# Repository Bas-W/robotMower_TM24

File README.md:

# robotMower_TM24
Robot lawn mower project for school.

# Notes
Some notes including the lessons we learned and the mistakes we found in our work can be found under [<b>*/Notes*</b>](/Notes.md)\
This contains some important information for anyone who wants to expand this project, **Please read this document**.

# Features
A list of features can be found under [<b>*/Features*</b>](/Features.md)

# Schematics, PCB
Schematics, along with footprints, can be found under [<b>*/Schematics*</b>](/Schematics).
These are designed in Fusion 360/Eagle, original Fusion/eagle Schematic, board and library files can be found under [***/Schematics/RoborMower_TM24/***](/Schematics/RoborMower_TM24/)

# Code
Code can be found under [***/Code***](/Code).
The final code for the ESP32 can be found under [***/Code/Final_V1.0***](/Code/Final_V1.0.0/).
The final code for the Attiny that read the HC-SR04 sensor can be fount under [***/Code/Test Sketches/ATtiny84_I2C-Slave-Ultrasonic_Test/***](/Code/Test%20Sketches/ATtiny84_I2C-Slave-Ultrasonic_Test/).

# Harware
A list of used components and modules will be made when the design is finalized.

# I²C Adress List
|Part|Address|
|----|-------|
|Current Sensor, Motor L|01000000 = 0x40|
|Current Sensor, Motor R|01000001 = 0x41|
|Current Sensor, Bat in|01000010 = 0x42|
|Current Sensor, 5V|01000011 = 0x43|
|Current Sensor, 3V3|01000100 = 0x44|
|Attiny, Ultrasone Sensors|00001000 = 0x8|

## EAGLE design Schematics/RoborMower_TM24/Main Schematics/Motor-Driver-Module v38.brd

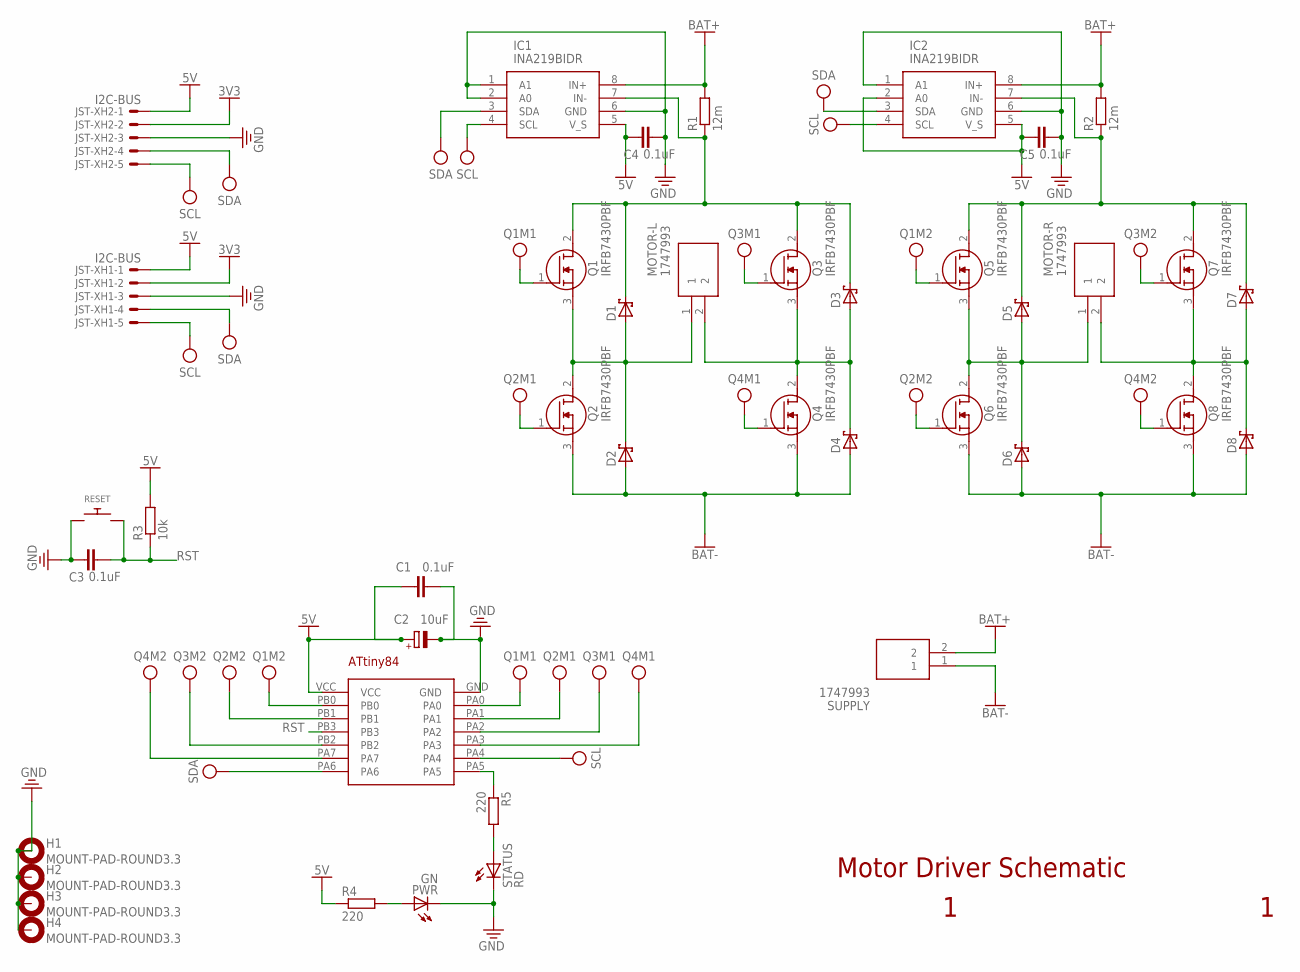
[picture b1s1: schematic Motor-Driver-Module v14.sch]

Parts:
C1: 0.1uF; C025-025X050
C2: 10uF; E5-10,5
C3, C4, C5: 0.1uF; C025-030X050
D1, D2, D3, D4, D5, D6, D7, D8: SCHOTTKY-DIODEDO41; DO41-10
H1, H2, H3, H4: MOUNT-PAD-ROUND3.3; 3,3-PAD
IC1, IC2: INA219BIDR; SOIC127P600X175-8N
JST-XH1, JST-XH2: I2C-BUS; JST-XH-05-PACKAGE-LONG-PAD
MOTOR-L: 1747993
MOTOR-R: 1747993
PWR: GN; LED5MM
Q1, Q2, Q3, Q4, Q5, Q6, Q7, Q8: IRFB7430PBF; TO254P483X1016X1994-3P
R1, R2: 12m; 0204/7
R3: 10k; 0204/7
R4, R5: 220; 0204/7
RESET: SWITCH_PUSHBUTTONEVQ-PE; TACT_PANA-EVQ
STATUS: RD; LED5MM
SUPPLY: 1747993
U$1: ATTINY84DIP; ATTINY84(DIP)

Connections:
3V3: JST-XH1.2, JST-XH2.2
5V: C1.1, C2.+, C4.1, C5.1, IC1.5 (V_S), IC2.2 (A0), IC2.5 (V_S), JST-XH1.1, JST-XH2.1, R3.2, R4.1, U$1.VCC
BAT+: IC1.8 (IN+), IC2.8 (IN+), R1.2, R2.2, SUPPLY.2
BAT-: D2.A, D4.A, D6.A, D8.A, Q2.3 (S), Q4.3 (S), Q6.3 (S), Q8.3 (S), SUPPLY.1
GND: C1.2, C2.-, C3.1, C4.2, C5.2, H1.B3,3, H2.B3,3, H3.B3,3, H4.B3,3, IC1.1 (A1), IC1.2 (A0), IC1.6 (GND), IC2.1 (A1), IC2.6 (GND), JST-XH1.3, JST-XH2.3, PWR.K (C), RESET.P$1, STATUS.K (C), U$1.GND
unnamed: D3.A, D4.C, MOTOR-L.2, Q3.3 (S), Q4.2 (D)
unnamed: D1.A, D2.C, MOTOR-L.1, Q1.3 (S), Q2.2 (D)
unnamed: D7.A, D8.C, MOTOR-R.2, Q7.3 (S), Q8.2 (D)
unnamed: D5.A, D6.C, MOTOR-R.1, Q5.3 (S), Q6.2 (D)
unnamed: D1.C, D3.C, IC1.7 (IN-), Q1.2 (D), Q3.2 (D), R1.1
unnamed: D5.C, D7.C, IC2.7 (IN-), Q5.2 (D), Q7.2 (D), R2.1
unnamed: R5.1, U$1.PA5
unnamed: R5.2, STATUS.A
unnamed: PWR.A, R4.2
Q1M1: Q1.1 (G), U$1.PA0
Q1M2: Q5.1 (G), U$1.PB0
Q2M1: Q2.1 (G), U$1.PA1
Q2M2: Q6.1 (G), U$1.PB1
Q3M1: Q3.1 (G), U$1.PA2
Q3M2: Q7.1 (G), U$1.PB2
Q4M1: Q4.1 (G), U$1.PA3
Q4M2: Q8.1 (G), U$1.PA7
RST: C3.2, R3.1, RESET.P$2, U$1.PB3
SCL: IC1.4 (SCL), IC2.4 (SCL), JST-XH1.5, JST-XH2.5, U$1.PA4
SDA: IC1.3 (SDA), IC2.3 (SDA), JST-XH1.4, JST-XH2.4, U$1.PA6

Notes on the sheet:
Motor Driver Schematic

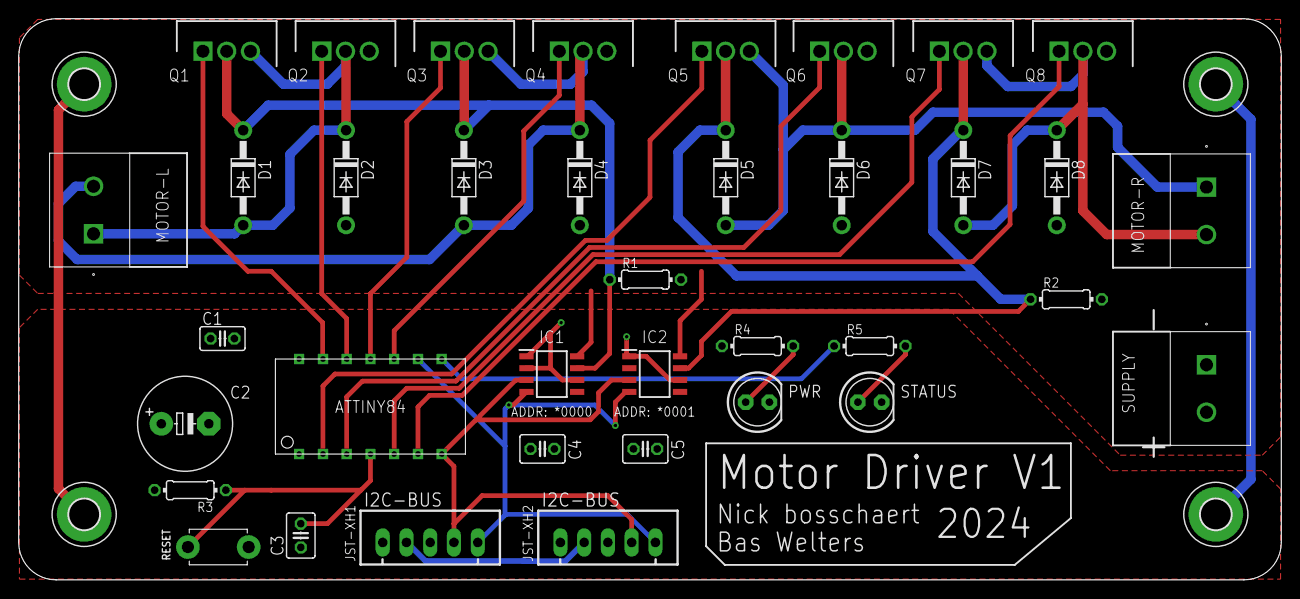
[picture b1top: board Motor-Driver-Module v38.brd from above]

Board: 2 copper layers, 135.0 x 60.0 mm, 41 parts (0 on the bottom side), 25 nets.

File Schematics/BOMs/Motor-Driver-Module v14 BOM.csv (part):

Part;Value;Device;Package;Description;ARROW_PART_NUMBER;ARROW_PRICE-STOCK;DESCRIPTION;HEIGHT;MANUFACTURER_NAME;MANUFACTURER_PART_NUMBER;MOUSER_PART_NUMBER;MOUSER_PRICE-STOCK;POPULARITY;SPICEPREFIX
C1;0.1uF;C-EU025-025X050;C025-025X050;CAPACITOR, European symbol;;;;;;;;;65;C
C2;10uF;CPOL-EUE5-10.5;E5-10,5;POLARIZED CAPACITOR, European symbol;;;;;;;;;23;C
C3;0.1uF;C-EU025-030X050;C025-030X050;CAPACITOR, European symbol;;;;;;;;;14;C
C4;0.1uF;C-EU025-030X050;C025-030X050;CAPACITOR, European symbol;;;;;;;;;14;C
C5;0.1uF;C-EU025-030X050;C025-030X050;CAPACITOR, European symbol;;;;;;;;;14;C
D1;;SCHOTTKY-DIODEDO41;DO41-10;Schottky Diode;;;;;;;;;;
D2;;SCHOTTKY-DIODEDO41;DO41-10;Schottky Diode;;;;;;;;;;
D3;;SCHOTTKY-DIODEDO41;DO41-10;Schottky Diode;;;;;;;;;;
D4;;SCHOTTKY-DIODEDO41;DO41-10;Schottky Diode;;;;;;;;;;
D5;;SCHOTTKY-DIODEDO41;DO41-10;Schottky Diode;;;;;;;;;;
D6;;SCHOTTKY-DIODEDO41;DO41-10;Schottky Diode;;;;;;;;;;
D7;;SCHOTTKY-DIODEDO41;DO41-10;Schottky Diode;;;;;;;;;;
D8;;SCHOTTKY-DIODEDO41;DO41-10;Schottky Diode;;;;;;;;;;
H1;MOUNT-PAD-ROUND3.3;MOUNT-PAD-ROUND3.3;3,3-PAD;MOUNTING PAD, round;;;;;;;;;1;
H2;MOUNT-PAD-ROUND3.3;MOUNT-PAD-ROUND3.3;3,3-PAD;MOUNTING PAD, round;;;;;;;;;1;
H3;MOUNT-PAD-ROUND3.3;MOUNT-PAD-ROUND3.3;3,3-PAD;MOUNTING PAD, round;;;;;;;;;1;
H4;MOUNT-PAD-ROUND3.3;MOUNT-PAD-ROUND3.3;3,3-PAD;MOUNTING PAD, round;;;;;;;;;1;
IC1;INA219BIDR;INA219BIDR;SOIC127P600X175-8N;26-V, Bidirectional, Zero-Drift, High-Side, I2C Out Current/Power Monitor;;;26-V, Bidirectional, Zero-Drift, High-Side, I2C Out Current/Power Monitor;1.75mm;Texas Instruments;INA219BIDR;595-INA219BIDR;https://www.mouser.co.uk/ProductDetail/Texas-Instruments/INA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;;
IC2;INA219BIDR;INA219BIDR;SOIC127P600X175-8N;26-V, Bidirectional, Zero-Drift, High-Side, I2C Out Current/Power Monitor;;;26-V, Bidirectional, Zero-Drift, High-Side, I2C Out Current/Power Monitor;1.75mm;Texas Instruments;INA219BIDR;595-INA219BIDR;https://www.mouser.co.uk/ProductDetail/Texas-Instruments/INA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;;
JST-XH1;I2C-BUS;JST-XH-05-PIN-LONG-PAD;JST-XH-05-PACKAGE-LONG-PAD;JST XH Connector 2 Pin;;;;;;;;;;
JST-XH2;I2C-BUS;JST-XH-05-PIN-LONG-PAD;JST-XH-05-PACKAGE-LONG-PAD;JST XH Connector 2 Pin;;;;;;;;;;
MOTOR-L;1747993;1747993;1747993;PCB header, nominal cross section: 2.5 mm?, color: green, nominal current: 12 A, rated voltage (III/2): 320 V, contact surface: Gold, type of contact: Male connector, Number of potentials: 2, Number of rows: 1, Number of positions per row: 2, number of connections: 2, product range: MSTBVA 2,5/..-G, pitch: 5.08 mm, mounting: Wave soldering, pin layout: Linear pinning, solder pin [P]: 3.9 mm, Stecksystem: CLASSIC COMBICON, Locking: without, type of packaging: packed in cardboard;;;PCB header, nominal cross section: 2.5 mm?, color: green, nominal current: 12 A, rated voltage (III/2): 320 V, contact surface: Gold, type of contact: Male connector, Number of potentials: 2, Number of rows: 1, Number of positions per row: 2, number of connections: 2, product range: MSTBVA 2,5/..-G, pitch: 5.08 mm, mounting: Wave soldering, pin layout: Linear pinning, solder pin [P]: 3.9 mm, Stecksystem: CLASSIC COMBICON, Locking: without, type of packaging: packed in cardboard;12.15mm;Phoenix Contact;1747993;651-1747993;https://www.mouser.co.uk/ProductDetail/Phoenix-Contact/17479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;;
MOTOR-R;1747993;1747993;1747993;PCB header, nominal cross section: 2.5 mm?, color: green, nominal current: 12 A, rated voltage (III/2): 320 V, contact surface: Gold, type of contact: Male connector, Number of potentials: 2, Number of rows: 1, Number of positions per row: 2, number of connections: 2, product range: MSTBVA 2,5/..-G, pitch: 5.08 mm, mounting: Wave soldering, pin layout: Linear pinning, solder pin [P]: 3.9 mm, Stecksystem: CLASSIC COMBICON, Locking: without, type of packaging: packed in cardboard;;;PCB header, nominal cross section: 2.5 mm?, color: green, nominal current: 12 A, rated voltage (III/2): 320 V, contact surface: Gold, type of contact: Male connector, Number of potentials: 2, Number of rows: 1, Number of positions per row: 2, number of connections: 2, product range: MSTBVA 2,5/..-G, pitch: 5.08 mm, mounting: Wave soldering, pin layout: Linear pinning, solder pin [P]: 3.9 mm, Stecksystem: CLASSIC COMBICON, Locking: without, type of packaging: packed in cardboard;12.15mm;Phoenix Contact;1747993;651-1747993;https://www.mouser.co.uk/ProductDetail/Phoenix-Contact/17479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;;
PWR;GN;LED5MM;LED5MM;LED;;;;;;;;;;
Q1;IRFB7430PBF;IRFB7430PBF;TO254P483X1016X1994-3P;Infineon IRFB7430PBF N-channel MOSFET, 195 A, 40 V StrongIRFET, 3-Pin TO-220AB;;;Infineon IRFB7430PBF N-channel MOSFET, 195 A, 40 V StrongIRFET, 3-Pin TO-220AB;4.83mm;Infineon;IRFB7430PBF;942-IRFB7430PBF;https://www.mouser.co.uk/ProductDetail/Infineon-Technologies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;;
Q2;IRFB7430PBF;IRFB7430PBF;TO254P483X1016X1994-3P;Infineon IRFB7430PBF N-channel MOSFET, 195 A, 40 V StrongIRFET, 3-Pin TO-220AB;;;Infineon IRFB7430PBF N-channel MOSFET, 195 A, 40 V StrongIRFET, 3-Pin TO-220AB;4.83mm;Infineon;IRFB7430PBF;942-IRFB7430PBF;https://www.mouser.co.uk/ProductDetail/Infineon-Technologies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;;
Q3;IRFB7430PBF;IRFB7430PBF;TO254P483X1016X1994-3P;Infineon IRFB7430PBF N-channel MOSFET, 195 A, 40 V StrongIRFET, 3-Pin TO-220AB;;;Infineon IRFB7430PBF N-channel MOSFET, 195 A, 40 V StrongIRFET, 3-Pin TO-220AB;4.83mm;Infineon;IRFB7430PBF;942-IRFB7430PBF;https://www.mouser.co.uk/ProductDetail/Infineon-Technologies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;;
Q4;IRFB7430PBF;IRFB7430PBF;TO254P483X1016X1994-3P;Infineon IRFB7430PBF N-channel MOSFET, 195 A, 40 V StrongIRFET, 3-Pin TO-220AB;;;Infineon IRFB7430PBF N-channel MOSFET, 195 A, 40 V StrongIRFET, 3-Pin TO-220AB;4.83mm;Infineon;IRFB7430PBF;942-IRFB7430PBF;https://www.mouser.co.uk/ProductDetail/Infineon-Technologies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;;
Q5;IRFB7430PBF;IRFB7430PBF;TO254P483X1016X1994-3P;Infineon IRFB7430PBF N-channel MOSFET, 195 A, 40 V StrongIRFET, 3-Pin TO-220AB;;;Infineon IRFB7430PBF N-channel MOSFET, 195 A, 40 V StrongIRFET, 3-Pin TO-220AB;4.83mm;Infineon;IRFB7430PBF;942-IRFB7430PBF;https://www.mouser.co.uk/ProductDetail/Infineon-Technologies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;;
Q6;IRFB7430PBF;IRFB7430PBF;TO254P483X1016X1994-3P;Infineon IRFB7430PBF N-channel MOSFET, 195 A, 40 V StrongIRFET, 3-Pin TO-220AB;;;Infineon IRFB7430PBF N-channel MOSFET, 195 A, 40 V StrongIRFET, 3-Pin TO-220AB;4.83mm;Infineon;IRFB7430PBF;942-IRFB7430PBF;https://www.mouser.co.uk/ProductDetail/Infineon-Technologies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;;
Q7;IRFB7430PBF;IRFB7430PBF;TO254P483X1016X1994-3P;Infineon IRFB7430PBF N-channel MOSFET, 195 A, 40 V StrongIRFET, 3-Pin TO-220AB;;;Infineon IRFB7430PBF N-channel MOSFET, 195 A, 40 V StrongIRFET, 3-Pin TO-220AB;4.83mm;Infineon;IRFB7430PBF;942-IRFB7430PBF;https://www.mouser.co.uk/ProductDetail/Infineon-Technologies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;;
Q8;IRFB7430PBF;IRFB7430PBF;TO254P483X1016X1994-3P;Infineon IRFB7430PBF N-channel MOSFET, 195 A, 40 V StrongIRFET, 3-Pin TO-220AB;;;Infineon IRFB7430PBF N-channel MOSFET, 195 A, 40 V StrongIRFET, 3-Pin TO-220AB;4.83mm;Infineon;IRFB7430PBF;942-IRFB7430PBF;https://www.mouser.co.uk/ProductDetail/Infineon-Technologies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;;
R1;12m;R-EU_0204/7;0204/7;RESISTOR, European symbol;;;;;;;;;79;R
R2;12m;R-EU_0204/7;0204/7;RESISTOR, European symbol;;;;;;;;;79;R
R3;10k;R-EU_0204/7;0204/7;RESISTOR, European symbol;;;;;;;;;79;R
R4;220;R-EU_0204/7;0204/7;RESISTOR, European symbol;;;;;;;;;79;R
R5;220;R-EU_0204/7;0204/7;RESISTOR, European symbol;;;;;;;;;79;R
RESET;;SWITCH_PUSHBUTTONEVQ-PE;TACT_PANA-EVQ;Buttons;;;;;;;;;;
STATUS;RD;LED5MM;LED5MM;LED;;;;;;;;;;
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
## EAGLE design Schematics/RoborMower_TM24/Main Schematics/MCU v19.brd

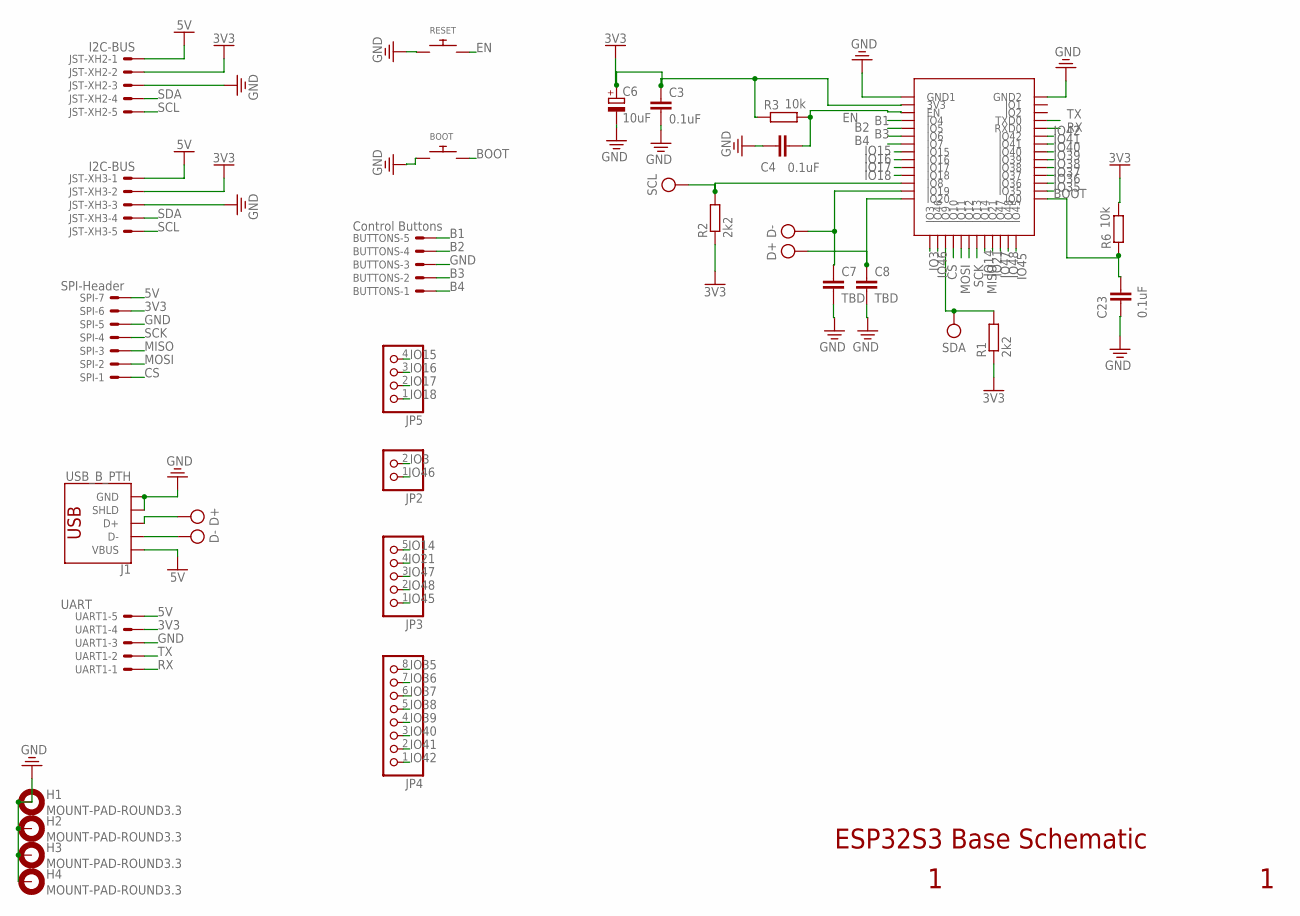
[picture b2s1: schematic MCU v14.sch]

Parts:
BOOT: SWITCH_PUSHBUTTONEVQ-PE; TACT_PANA-EVQ
BUTTONS: Control Buttons; JST-XH-05-PACKAGE-LONG-PAD
C3, C4, C23: 0.1uF; C025-030X050
C6: 10uF; CAPPRD508W65D1000H1100B
C7, C8: TBD; C025-030X050
H1, H2, H3, H4: MOUNT-PAD-ROUND3.3; 3,3-PAD
J1: USB_B_PTH; USB-B-PTH
JP2: PINHD-1X2; 1X02
JP3: PINHD-1X55X2MM; 1_05X2MM
JP4: PINHD-1X8; 1X08
JP5: PINHD-1X4; 1X04
JST-XH2, JST-XH3: I2C-BUS; JST-XH-05-PACKAGE-LONG-PAD
R1, R2: 2k2; 0204/5
R3, R6: 10k; 0204/7
RESET: SWITCH_PUSHBUTTONEVQ-PE; TACT_PANA-EVQ
SPI: SPI-Header; JST-XH-07-PACKAGE-LONG-PAD
U$1: ESP32-S3-WROOM-1
UART1: UART; JST-XH-05-PACKAGE-ROUND-PAD

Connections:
3V3: C3.1, C6.1 (+), JST-XH2.2, JST-XH3.2, R1.1, R2.1, R3.1, R6.2, SPI.6, U$1.3V3, UART1.4
5V: J1.VBUS, JST-XH2.1, JST-XH3.1, SPI.7, UART1.5
B1: BUTTONS.5, U$1.IO4
B2: BUTTONS.4, U$1.IO5
B3: BUTTONS.2, U$1.IO6
B4: BUTTONS.1, U$1.IO7
BOOT: BOOT.P$2, C23.2, R6.1, U$1.IO0
CS: SPI.1, U$1.IO10
D+: C8.1, J1.D+, U$1.IO20
D-: C7.1, J1.D-, U$1.IO19
EN: C4.2, R3.2, RESET.P$2, U$1.EN
GND: BOOT.P$1, BUTTONS.3, C3.2, C4.1, C6.2 (-), C7.2, C8.2, C23.1, H1.B3,3, H2.B3,3, H3.B3,3, H4.B3,3, J1.GND, J1.SHLD1 (SHLD), J1.SHLD2 (SHLD), JST-XH2.3, JST-XH3.3, RESET.P$1, SPI.5, U$1.GND1, U$1.GND2, UART1.3
IO3: JP2.2, U$1.IO3
IO14: JP3.5, U$1.IO14
IO15: JP5.4, U$1.IO15
IO16: JP5.3, U$1.IO16
IO17: JP5.2, U$1.IO17
IO18: JP5.1, U$1.IO18
IO21: JP3.4, U$1.IO21
IO35: JP4.8, U$1.IO35
IO36: JP4.7, U$1.IO36
IO37: JP4.6, U$1.IO37
IO38: JP4.5, U$1.IO38
IO39: JP4.4, U$1.IO39
IO40: JP4.3, U$1.IO40
IO41: JP4.2, U$1.IO41
IO42: JP4.1, U$1.IO42
IO45: JP3.1, U$1.IO45
IO46: JP2.1, U$1.IO46
IO47: JP3.3, U$1.IO47
IO48: JP3.2, U$1.IO48
MISO: SPI.3, U$1.IO13
MOSI: SPI.2, U$1.IO11
RX: U$1.RXD0, UART1.1
SCK: SPI.4, U$1.IO12
SCL: JST-XH2.5, JST-XH3.5, R2.2, U$1.IO8
SDA: JST-XH2.4, JST-XH3.4, R1.2, U$1.IO9
TX: U$1.TXD0, UART1.2

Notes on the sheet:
ESP32S3 Base Schematic

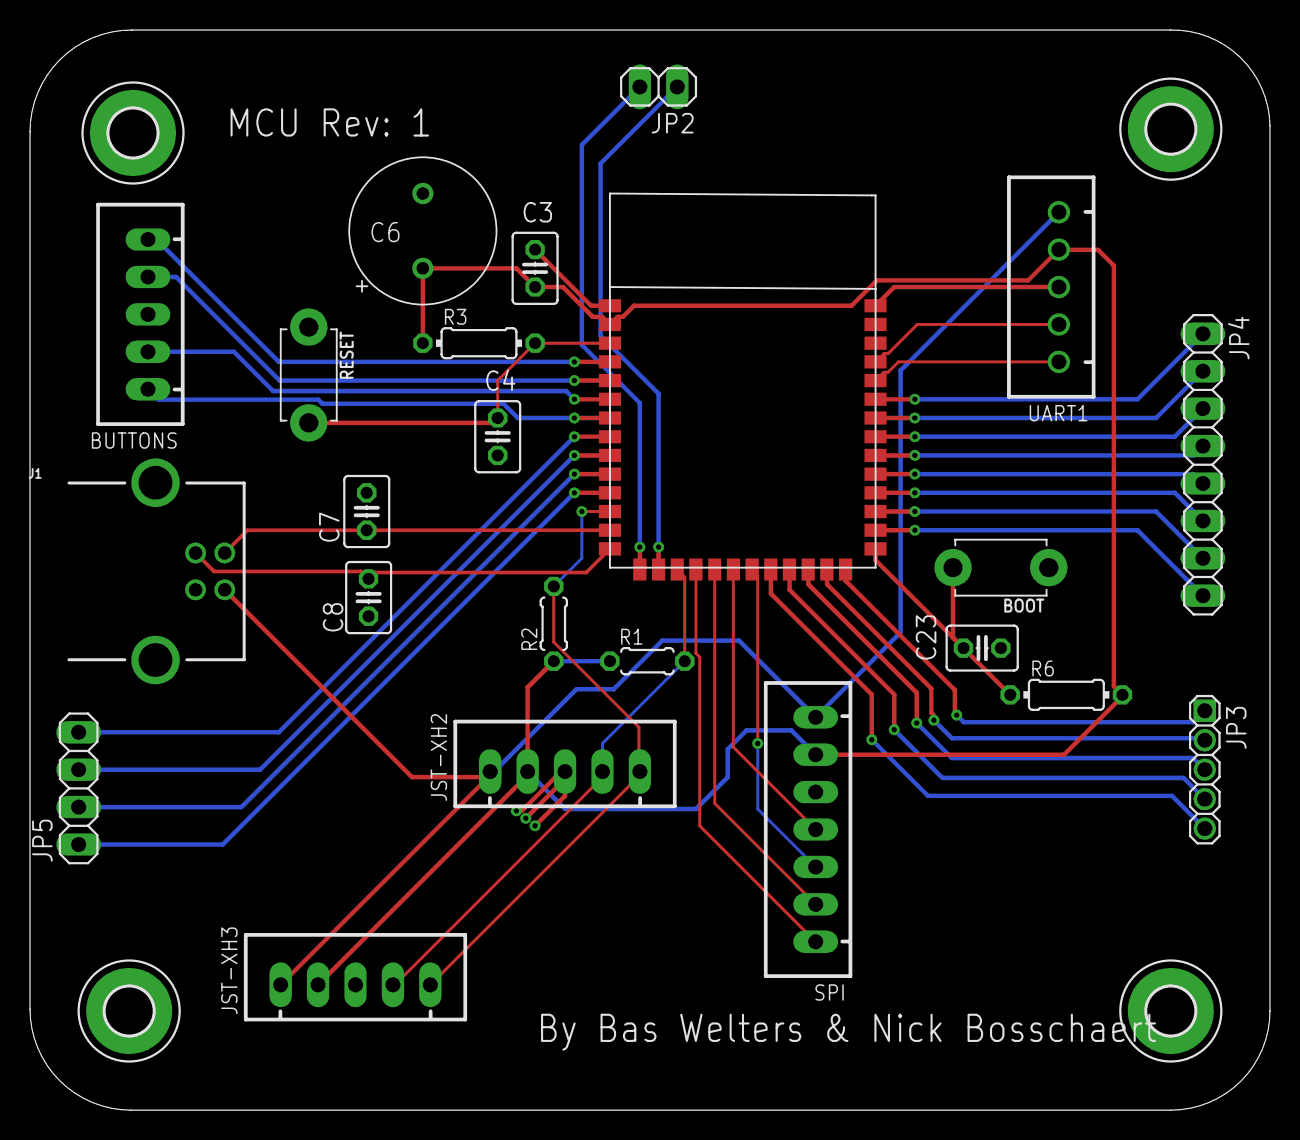
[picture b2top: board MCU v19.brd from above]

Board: 2 copper layers, 84.2 x 73.3 mm, 27 parts (0 on the bottom side), 38 nets.

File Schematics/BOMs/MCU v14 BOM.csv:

Part;Value;Device;Package;Description;CATEGORY;MANUFACTURER;MPN;OPERATING_TEMP;PART_STATUS;POPULARITY;PROD_ID;ROHS_COMPLIANT;SERIES;SF_ID;SPICEPREFIX;SUB-CATEGORY;THERMALLOSS;TYPE;VOLTAGE_RATING
BOOT;;SWITCH_PUSHBUTTONEVQ-PE;TACT_PANA-EVQ;Buttons;;;;;;;;;;;;;;;
BUTTONS;Control Buttons;JST-XH-05-PIN-LONG-PAD;JST-XH-05-PACKAGE-LONG-PAD;JST XH Connector 2 Pin;;;;;;;;;;;;;;;
C3;0.1uF;C-EU025-030X050;C025-030X050;CAPACITOR, European symbol;;;;;;14;;;;;C;;;;
C4;0.1uF;C-EU025-030X050;C025-030X050;CAPACITOR, European symbol;;;;;;14;;;;;C;;;;
C6;10uF;C-POL_RADIAL-11MM-DIA;CAPPRD508W65D1000H1100B;Capacitor Polarised - Generic;Capacitor;;;;;;;;;;;;;;
C7;TBD;C-EU025-030X050;C025-030X050;CAPACITOR, European symbol;;;;;;14;;;;;C;;;;
C8;TBD;C-EU025-030X050;C025-030X050;CAPACITOR, European symbol;;;;;;14;;;;;C;;;;
C23;0.1uF;C-EU025-030X050;C025-030X050;CAPACITOR, European symbol;;;;;;14;;;;;C;;;;
H1;MOUNT-PAD-ROUND3.3;MOUNT-PAD-ROUND3.3;3,3-PAD;MOUNTING PAD, round;;;;;;1;;;;;;;;;
H2;MOUNT-PAD-ROUND3.3;MOUNT-PAD-ROUND3.3;3,3-PAD;MOUNTING PAD, round;;;;;;1;;;;;;;;;
H3;MOUNT-PAD-ROUND3.3;MOUNT-PAD-ROUND3.3;3,3-PAD;MOUNTING PAD, round;;;;;;1;;;;;;;;;
H4;MOUNT-PAD-ROUND3.3;MOUNT-PAD-ROUND3.3;3,3-PAD;MOUNTING PAD, round;;;;;;1;;;;;;;;;
J1;USB_B_PTH;USB_B_PTH;USB-B-PTH;USB Type B Connector;;;;;;;CONN-08278;;;PRT-00139;;;;;
JP2;;PINHD-1X2;1X02;PIN HEADER;;;;;;98;;;;;;;;;
JP3;;PINHD-1X55X2MM;1_05X2MM;PIN HEADER;;;;;;0;;;;;;;;;
JP4;;PINHD-1X8;1X08;PIN HEADER;;;;;;67;;;;;;;;;
JP5;;PINHD-1X4;1X04;PIN HEADER;;;;;;91;;;;;;;;;
JST-XH2;I2C-BUS;JST-XH-05-PIN-LONG-PAD;JST-XH-05-PACKAGE-LONG-PAD;JST XH Connector 2 Pin;;;;;;;;;;;;;;;
JST-XH3;I2C-BUS;JST-XH-05-PIN-LONG-PAD;JST-XH-05-PACKAGE-LONG-PAD;JST XH Connector 2 Pin;;;;;;;;;;;;;;;
R1;2k2;R-EU_0204/5;0204/5;RESISTOR, European symbol;;;;;;35;;;;;R;;;;
R2;2k2;R-EU_0204/5;0204/5;RESISTOR, European symbol;;;;;;35;;;;;R;;;;
R3;10k;R-EU_0204/7;0204/7;RESISTOR, European symbol;;;;;;79;;;;;R;;;;
R6;10k;R-EU_0204/7;0204/7;RESISTOR, European symbol;;;;;;79;;;;;R;;;;
RESET;;SWITCH_PUSHBUTTONEVQ-PE;TACT_PANA-EVQ;Buttons;;;;;;;;;;;;;;;
SPI;SPI-Header;JST-XH-07-PIN-LONG-PAD;JST-XH-07-PACKAGE-LONG-PAD;JST XH Connector 2 Pin;;;;;;;;;;;;;;;
U$1;ESP32-S3-WROOM-1;ESP32-S3-WROOM-1;ESP32-S3-WROOM-1;;;;;;;;;;;;;;;;
UART1;UART;JST-XH-05-PIN-ROUND-PAD;JST-XH-05-PACKAGE-ROUND-PAD;JST XH Connector 2 Pin;;;;;;;;;;;;;;;

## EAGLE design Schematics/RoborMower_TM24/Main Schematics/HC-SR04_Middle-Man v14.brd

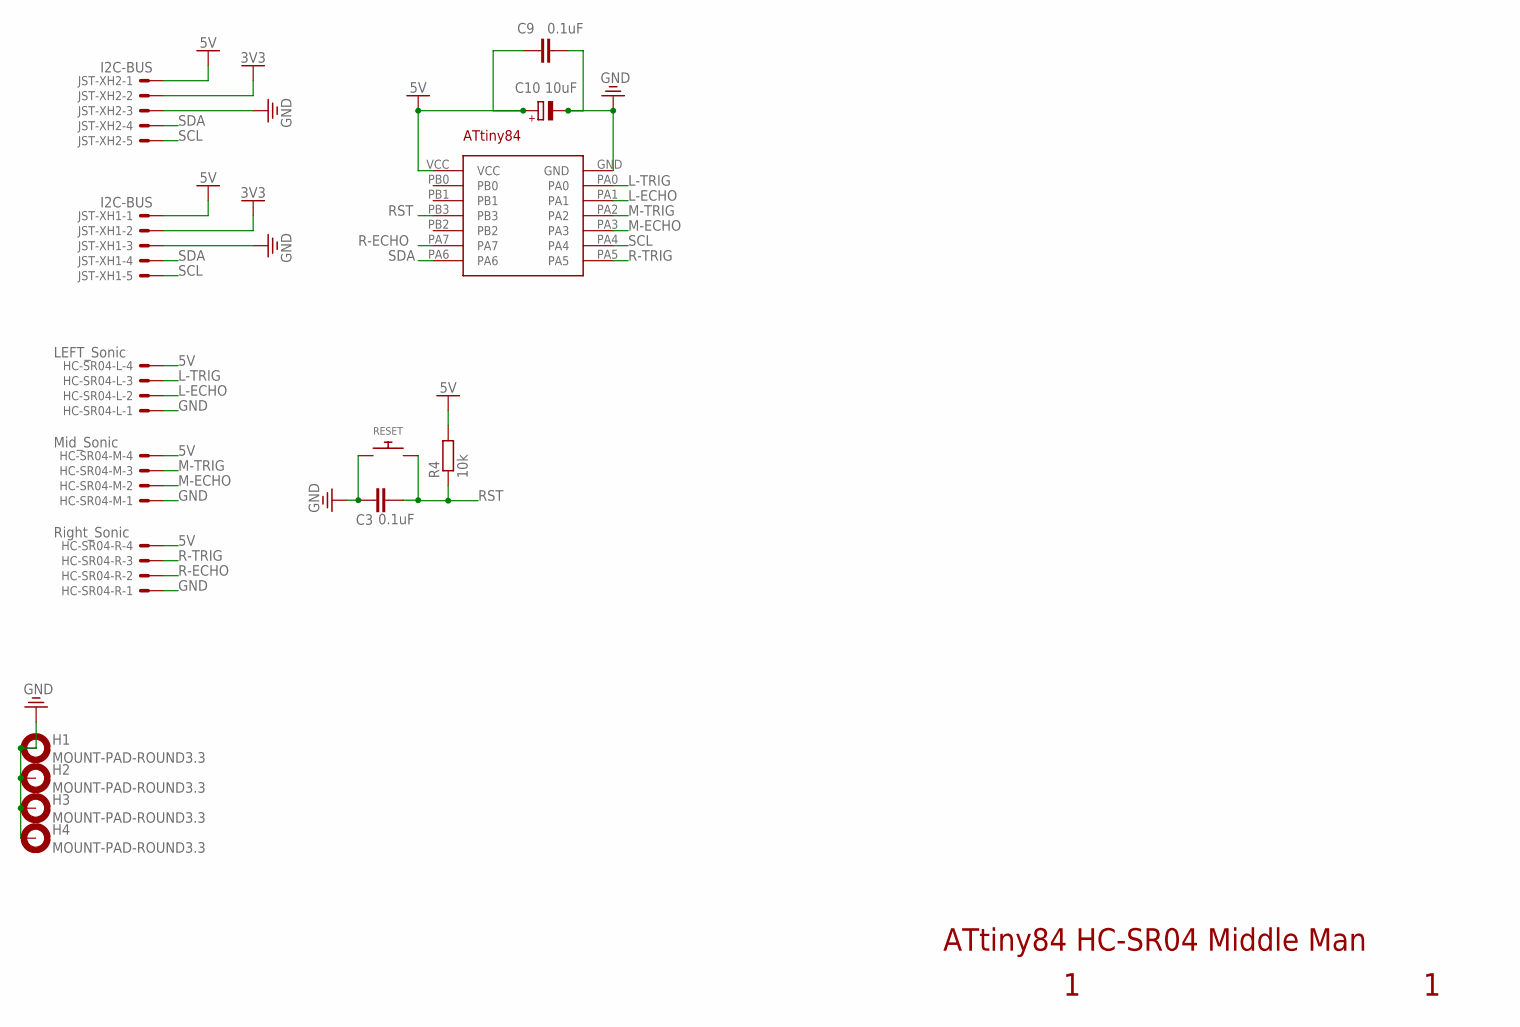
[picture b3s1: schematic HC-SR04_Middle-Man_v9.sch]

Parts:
C3: 0.1uF; C025-030X050
C9: 0.1uF; C025-025X050
C10: 10uF; E5-10,5
H1, H2, H3, H4: MOUNT-PAD-ROUND3.3; 3,3-PAD
HC-SR04-L: LEFT_Sonic; JST-XH-04-PACKAGE-LONG-PAD
HC-SR04-M: Mid_Sonic; JST-XH-04-PACKAGE-LONG-PAD
HC-SR04-R: Right_Sonic; JST-XH-04-PACKAGE-LONG-PAD
JST-XH1, JST-XH2: I2C-BUS; JST-XH-05-PACKAGE-LONG-PAD
R4: 10k; 0204/7
RESET: SWITCH_PUSHBUTTONEVQ-PE; TACT_PANA-EVQ
U$3: ATTINY84DIP; ATTINY84(DIP)

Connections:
3V3: JST-XH1.2, JST-XH2.2
5V: C9.1, C10.+, HC-SR04-L.4, HC-SR04-M.4, HC-SR04-R.4, JST-XH1.1, JST-XH2.1, R4.2, U$3.VCC
GND: C3.1, C9.2, C10.-, H1.B3,3, H2.B3,3, H3.B3,3, H4.B3,3, HC-SR04-L.1, HC-SR04-M.1, HC-SR04-R.1, JST-XH1.3, JST-XH2.3, RESET.P$1, U$3.GND
L-ECHO: HC-SR04-L.2, U$3.PA1
L-TRIG: HC-SR04-L.3, U$3.PA0
M-ECHO: HC-SR04-M.2, U$3.PA3
M-TRIG: HC-SR04-M.3, U$3.PA2
R-ECHO: HC-SR04-R.2, U$3.PA7
R-TRIG: HC-SR04-R.3, U$3.PA5
RST: C3.2, R4.1, RESET.P$2, U$3.PB3
SCL: JST-XH1.5, JST-XH2.5, U$3.PA4
SDA: JST-XH1.4, JST-XH2.4, U$3.PA6

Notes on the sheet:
ATtiny84 HC-SR04 Middle Man

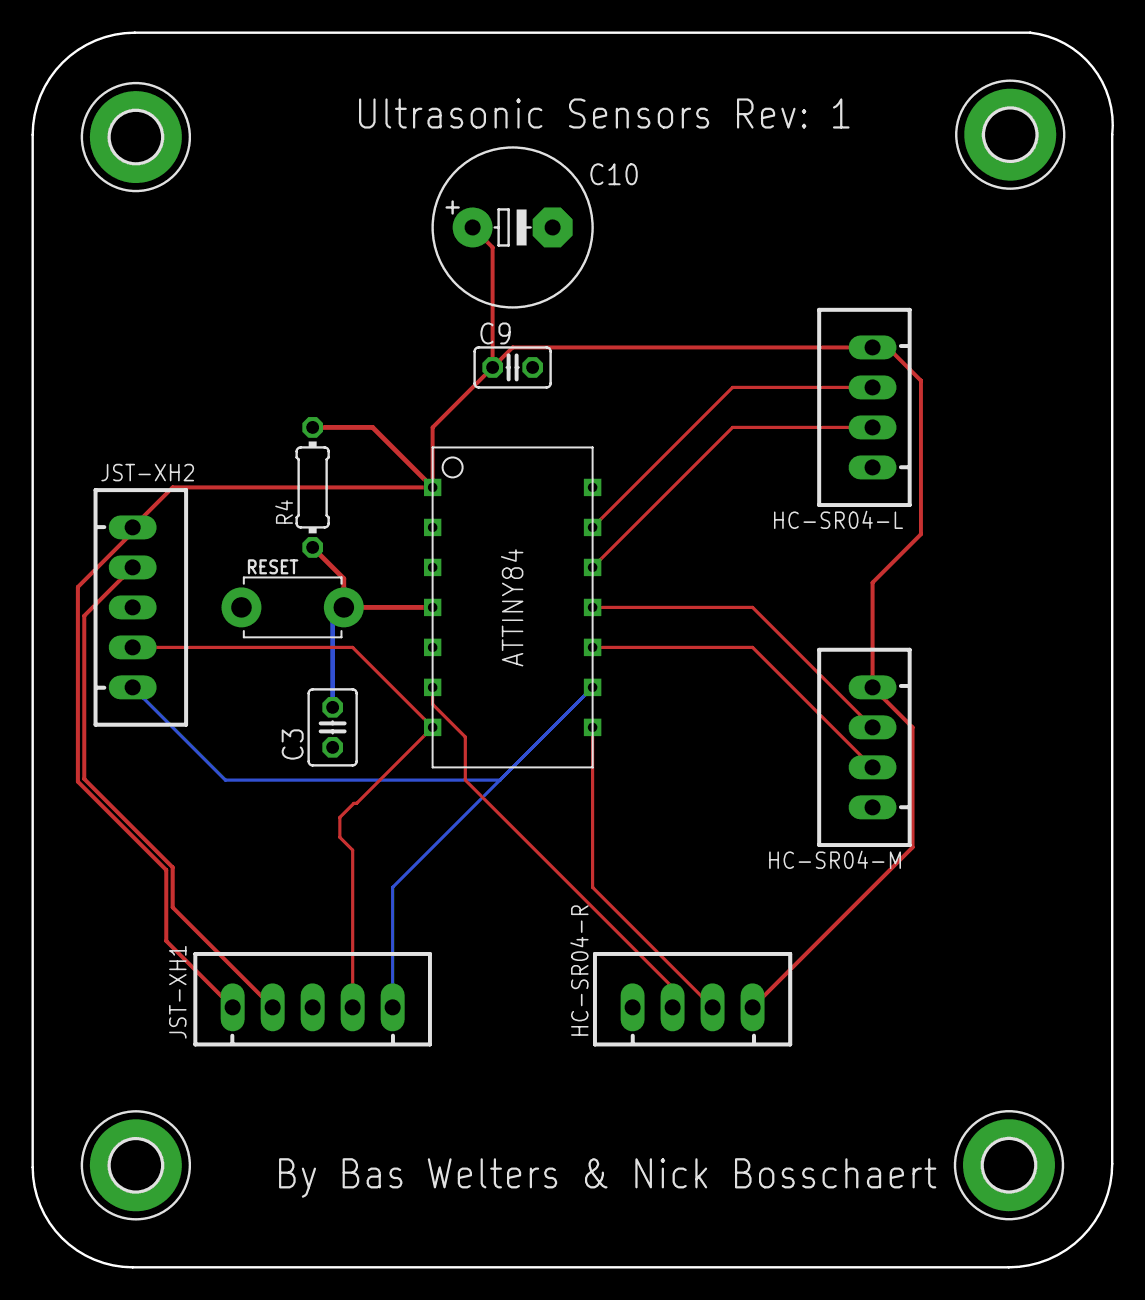
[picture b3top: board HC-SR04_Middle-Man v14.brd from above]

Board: 2 copper layers, 68.6 x 78.4 mm, 15 parts (0 on the bottom side), 12 nets.

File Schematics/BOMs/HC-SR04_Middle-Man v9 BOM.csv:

Part;Value;Device;Package;Description;POPULARITY;SPICEPREFIX
C3;0.1uF;C-EU025-030X050;C025-030X050;CAPACITOR, European symbol;14;C
C9;0.1uF;C-EU025-025X050;C025-025X050;CAPACITOR, European symbol;65;C
C10;10uF;CPOL-EUE5-10.5;E5-10,5;POLARIZED CAPACITOR, European symbol;23;C
H1;MOUNT-PAD-ROUND3.3;MOUNT-PAD-ROUND3.3;3,3-PAD;MOUNTING PAD, round;1;
H2;MOUNT-PAD-ROUND3.3;MOUNT-PAD-ROUND3.3;3,3-PAD;MOUNTING PAD, round;1;
H3;MOUNT-PAD-ROUND3.3;MOUNT-PAD-ROUND3.3;3,3-PAD;MOUNTING PAD, round;1;
H4;MOUNT-PAD-ROUND3.3;MOUNT-PAD-ROUND3.3;3,3-PAD;MOUNTING PAD, round;1;
HC-SR04-L;LEFT_Sonic;JST-XH-04-PIN-LONG-PAD;JST-XH-04-PACKAGE-LONG-PAD;JST XH Connector 2 Pin;;
HC-SR04-M;Mid_Sonic;JST-XH-04-PIN-LONG-PAD;JST-XH-04-PACKAGE-LONG-PAD;JST XH Connector 2 Pin;;
HC-SR04-R;Right_Sonic;JST-XH-04-PIN-LONG-PAD;JST-XH-04-PACKAGE-LONG-PAD;JST XH Connector 2 Pin;;
JST-XH1;I2C-BUS;JST-XH-05-PIN-LONG-PAD;JST-XH-05-PACKAGE-LONG-PAD;JST XH Connector 2 Pin;;
JST-XH2;I2C-BUS;JST-XH-05-PIN-LONG-PAD;JST-XH-05-PACKAGE-LONG-PAD;JST XH Connector 2 Pin;;
R4;10k;R-EU_0204/7;0204/7;RESISTOR, European symbol;79;R
RESET;;SWITCH_PUSHBUTTONEVQ-PE;TACT_PANA-EVQ;Buttons;;
U$3;ATTINY84DIP;ATTINY84DIP;ATTINY84(DIP);;;

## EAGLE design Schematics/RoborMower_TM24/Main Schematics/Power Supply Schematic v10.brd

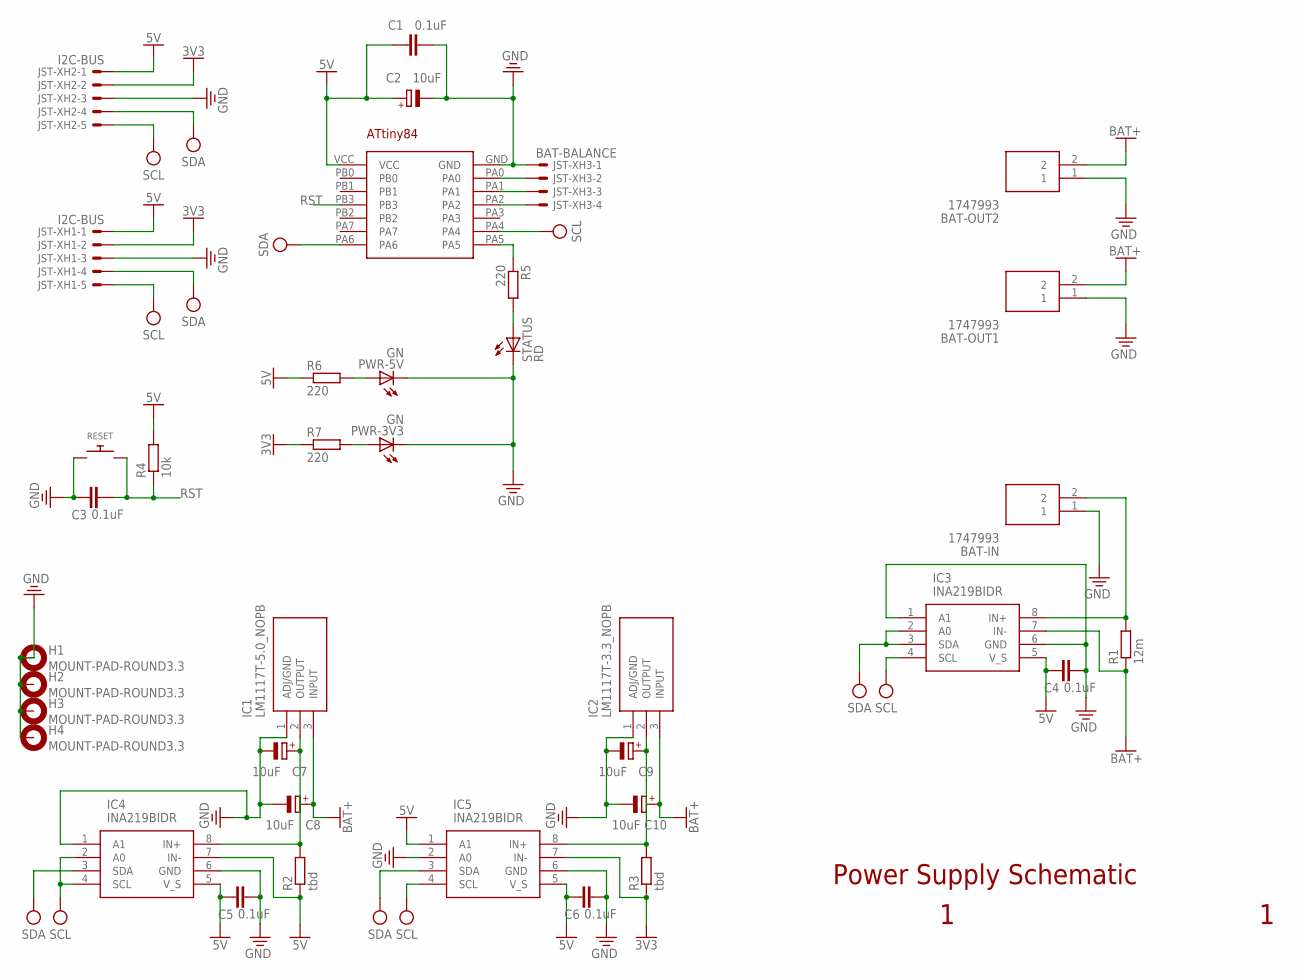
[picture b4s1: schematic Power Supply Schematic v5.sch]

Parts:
BAT-IN: 1747993
BAT-OUT1, BAT-OUT2: 1747993
C1: 0.1uF; C025-025X050
C2, C7, C8, C9, C10: 10uF; E5-10,5
C3, C4, C5, C6: 0.1uF; C025-030X050
H1, H2, H3, H4: MOUNT-PAD-ROUND3.3; 3,3-PAD
IC1: LM1117T-5.0_NOPB; TO254P470X1028X1955-3P
IC2: LM1117T-3.3_NOPB; TO254P470X1028X1955-3P
IC3, IC4, IC5: INA219BIDR; SOIC127P600X175-8N
JST-XH1, JST-XH2: I2C-BUS; JST-XH-05-PACKAGE-LONG-PAD
JST-XH3: BAT-BALANCE; JST-XH-04-PACKAGE-LONG-PAD
PWR-3V3, PWR-5V: GN; LED5MM
R1: 12m; 0204/7
R2, R3: tbd; 0204/7
R4: 10k; 0204/7
R5, R6, R7: 220; 0204/7
RESET: SWITCH_PUSHBUTTONEVQ-PE; TACT_PANA-EVQ
STATUS: RD; LED5MM
U$1: ATTINY84DIP; ATTINY84(DIP)

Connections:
3V3: IC5.7 (IN-), JST-XH1.2, JST-XH2.2, R3.1, R7.1
5V: C1.1, C2.+, C4.1, C5.1, C6.1, IC3.5 (V_S), IC4.5 (V_S), IC4.7 (IN-), IC5.1 (A1), IC5.5 (V_S), JST-XH1.1, JST-XH2.1, R2.1, R4.2, R6.1, U$1.VCC
BAT+: BAT-OUT1.2, BAT-OUT2.2, C8.+, C10.+, IC1.3 (INPUT), IC2.3 (INPUT), IC3.7 (IN-), R1.1
GND: BAT-IN.1, BAT-OUT1.1, BAT-OUT2.1, C1.2, C2.-, C3.1, C4.2, C5.2, C6.2, C7.-, C8.-, C9.-, C10.-, H1.B3,3, H2.B3,3, H3.B3,3, H4.B3,3, IC1.1 (ADJ/GND), IC2.1 (ADJ/GND), IC3.1 (A1), IC3.6 (GND), IC4.1 (A1), IC4.6 (GND), IC5.2 (A0), IC5.6 (GND), JST-XH1.3, JST-XH2.3, JST-XH3.1, PWR-3V3.K (C), PWR-5V.K (C), RESET.P$1, STATUS.K (C), U$1.GND
unnamed: BAT-IN.2, IC3.8 (IN+), R1.2
unnamed: JST-XH3.2, U$1.PA0
unnamed: JST-XH3.3, U$1.PA1
unnamed: JST-XH3.4, U$1.PA2
unnamed: C7.+, IC1.2 (OUTPUT), IC4.8 (IN+), R2.2
unnamed: C9.+, IC2.2 (OUTPUT), IC5.8 (IN+), R3.2
unnamed: R5.1, U$1.PA5
unnamed: R5.2, STATUS.A
unnamed: PWR-5V.A, R6.2
unnamed: PWR-3V3.A, R7.2
RST: C3.2, R4.1, RESET.P$2, U$1.PB3
SCL: IC3.4 (SCL), IC4.2 (A0), IC4.4 (SCL), IC5.4 (SCL), JST-XH1.5, JST-XH2.5, U$1.PA4
SDA: IC3.2 (A0), IC3.3 (SDA), IC4.3 (SDA), IC5.3 (SDA), JST-XH1.4, JST-XH2.4, U$1.PA6

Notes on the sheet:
Power Supply Schematic

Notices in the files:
parts and their libraries:
SparkFun-Connectors: Licensing: Creative Commons ShareAlike 4.0 International - https://creativecommons.org/licenses/by-sa/4.0
